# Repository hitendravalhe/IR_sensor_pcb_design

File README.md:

# IR_sensor

# IR Sensor PCB Design with LM35

This repository contains the design files and documentation for an Infrared (IR) sensor PCB with an integrated LM35 temperature sensor. This project aims to provide a cost-effective and reliable solution for IR sensing applications, with the added feature of temperature measurement using the LM35 sensor.

## Table of Contents
- [Overview](#overview)
- [Features](#features)
- [Schematic](#schematic)
- [PCB Layout](#pcb-layout)
- [Bill of Materials](#bill-of-materials)
- [Assembly Instructions](#assembly-instructions)
- [License](#license)

## Overview

Infrared (IR) sensors are commonly used for a wide range of applications, including proximity detection, object tracking, and obstacle avoidance. This project presents a PCB design that combines an IR sensor with an LM35 temperature sensor, providing both IR sensing capabilities and temperature measurement in a single module.

## Features

- IR sensor for reliable proximity detection.
- Integrated LM35 temperature sensor for accurate temperature measurement.
- Compact PCB design for easy integration into your projects.
- Designed for easy assembly and compatibility with common components.

## Schematic

The schematic above illustrates the connections and components used in the IR sensor PCB design. It includes the IR sensor module, LM35 temperature sensor, power supply, and output connections. You can find the detailed schematic file in the [schematics](schematics) directory.

## PCB Layout

The PCB layout file and design files can be found in the [pcb_design](pcb_design) directory. This layout has been optimized for easy assembly and compatibility with standard PCB manufacturing processes.

## Bill of Materials

For a list of components required to assemble the PCB, please refer to the [Bill of Materials](docs/bill_of_materials.md) document. This document includes part numbers, quantities, and recommended suppliers.

## Assembly Instructions

Detailed assembly instructions can be found in the [Assembly Instructions](docs/assembly_instructions.md) document. It provides step-by-step guidance for soldering components onto the PCB and ensuring a successful assembly process.

## License

This project is licensed under the MIT License - see the [LICENSE](LICENSE) file for details.

---

Feel free to contribute, report issues, or suggest improvements by creating a pull request or opening an issue. We welcome collaboration to enhance the functionality and usability of this IR sensor PCB design.

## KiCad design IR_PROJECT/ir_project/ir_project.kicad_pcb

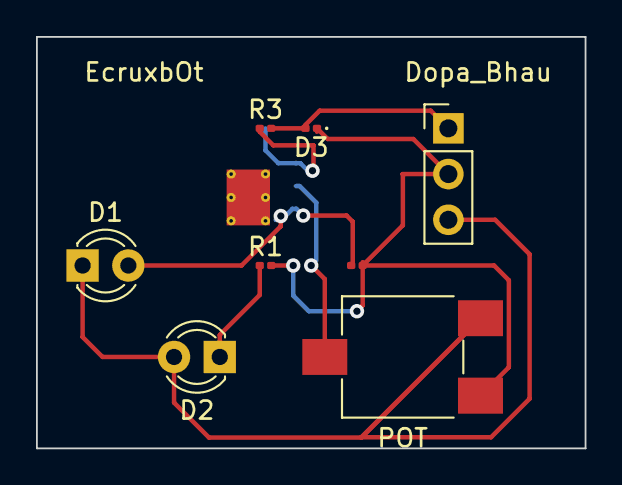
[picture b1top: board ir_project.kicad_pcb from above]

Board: 2 copper layers, 30.5 x 22.9 mm, 9 parts (1 on the bottom side), 7 nets.

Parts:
D1: D_Photo; LED_D3.0mm_IRBlack
D2: IR204A; LED_D3.0mm_IRBlack
D3: LED; LED_0201_0603Metric
J1: Conn_01x03_Pin; PinHeader_1x03_P2.54mm_Vertical
POT: R_Potentiometer; Potentiometer_ACP_CA6-VSMD_Vertical
R1, R2, R3: R; R_0201_0603Metric
U1: LM358; HSOP-8-1EP_3.9x4.9mm_P1.27mm_EP2.41x3.1mm_ThermalVias

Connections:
+5V: D1.1 (K), D2.2 (A), J1.3, POT.1
/O/P: D3.2 (A), J1.1, R3.2
GND: D3.1 (K), J1.2, POT.3, R1.2, R2.2
unnamed: D1.2 (A), R2.1, U1.3 (+)
unnamed: D2.1 (K), R1.1
unnamed: R3.1, U1.1
unnamed: POT.2, U1.2 (-)

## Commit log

2023-09-03 README.md
